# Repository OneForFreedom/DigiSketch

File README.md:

# DigiSketch
It's an etchasketch, gone digital!

Two rotary knobs, One for X axis and one for Y axis and one switch to reset.

I made this because I saw a video on someone using a physical etchasketch, and I thought to myself, hmmm what if I made that - DIGITAL!

so here it is!

Full 3D Model(s)

# BILL OF MATERIALS (BOM)
| Item                | Price (GBP) | Price (USD) | Link |
|---------------------|-------------|-------------|------|
| Solder              | 1.59        | 2.18        | [Link](https://www.aliexpress.com/item/1005008582739945.html?spm=a2g0o.cart.0.0.57e238dah0co8Q&mp=1&pdp_npi=5%40dis%21GBP%21GBP%201.56%21GBP%201.51%21%21GBP%201.51%21%21%21%40211b6c1917517505945503287e3f4d%2112000045828254978%21ct%21UK%216063356903%21%211%210) |
| Solder Cleaner      | 1.45        | 1.99        | [Link](https://www.aliexpress.com/item/1005008139056408.html?spm=a2g0o.cart.0.0.57e238dah0co8Q&mp=1&pdp_npi=5%40dis%21GBP%21GBP%201.45%21GBP%201.45%21%21GBP%201.31%21%21%21%40211b6c1917517505945503287e3f4d%2112000043955012936%21ct%21UK%216063356903%21%211%210) |
| Solder Holder       | 1.74        | 2.38        | [Link](https://www.aliexpress.com/item/1005008060490020.html?spm=a2g0o.cart.0.0.57e238dah0co8Q&mp=1&pdp_npi=5%40dis%21GBP%21GBP%203.62%21GBP%201.74%21%21GBP%201.57%21%21%21%40211b6c1917517505945503287e3f4d%2112000043495814700%21ct%21UK%216063356903%21%211%210) |
| OLED Screen         | 4           | 5.48        | [Link](https://www.aliexpress.com/item/1005008315281577.html?spm=a2g0o.cart.0.0.57e238daS8hq2S&mp=1&pdp_npi=5%40dis%21GBP%21GBP%206.35%21GBP%204.31%21%21GBP%204.31%21%21%21%40211b80e117517562457068912e2b41%2112000044585026991%21ct%21UK%216063356903%21%211%210) |
| Keycaps             | 1.59        | 2.18        | [Link](https://www.aliexpress.com/item/1005005513800132.html?spm=a2g0o.cart.0.0.57e238daS8hq2S&mp=1&pdp_npi=5%40dis%21GBP%21GBP%201.59%21GBP%201.59%21%21GBP%201.59%21%21%21%40211b80e117517562457068912e2b41%2112000033370341351%21ct%21UK%216063356903%21%211%210) |
| Switches            | 1.1         | 1.51        | [Link](https://www.aliexpress.com/item/1005005371211477.html?spm=a2g0o.cart.0.0.57e238daS8hq2S&mp=1&pdp_npi=5%40dis%21GBP%21GBP%201.10%21GBP%201.10%21%21GBP%201.10%21%21%21%40211b80e117517562457068912e2b41%2112000032783075056%21ct%21UK%216063356903%21%211%210&pdp_ext_f=%7B%22cart2PdpParams%22%3A%7B%22pdpBusinessMode%22%3A%22retail%22%7D%7D) |
| Pico                | 1.71        | 2.34        | [Link](https://www.aliexpress.com/item/1005003371056277.html?spm=a2g0o.cart.0.0.57e238daS8hq2S&mp=1&pdp_npi=5%40dis%21GBP%21GBP%201.71%21GBP%201.71%21%21GBP%201.71%21%21%21%40211b80e117517562457068912e2b41%2112000029224170853%21ct%21UK%216063356903%21%211%210) |
| EC11 Cap            | 1.04        | 1.42        | [Link](https://www.aliexpress.com/item/10000056483250.html?spm=a2g0o.cart.0.0.57e238daS8hq2S&mp=1&pdp_npi=5%40dis%21GBP%21GBP%201.04%21GBP%201.04%21%21GBP%201.04%21%21%21%40211b80e117517562457068912e2b41%2112000046133170771%21ct%21UK%216063356903%21%211%210) |
| EC11                | 1.96        | 2.68        | [Link](https://www.aliexpress.com/item/10000056483250.html?spm=a2g0o.cart.0.0.57e238daS8hq2S&mp=1&pdp_npi=5%40dis%21GBP%21GBP%201.96%21GBP%201.96%21%21GBP%201.96%21%21%21%40211b80e117517563008441721e2b41%2112000046133170768%21ct%21UK%216063356903%21%211%210) |
| Keycap Puller       | 1.72        | 2.36        | [Link](https://www.aliexpress.com/item/1005008979101146.html?spm=a2g0o.cart.0.0.57e238daS8hq2S&mp=1&pdp_npi=5%40dis%21GBP%21GBP%201.72%21GBP%201.72%21%21GBP%201.72%21%21%21%40211b80e117517563008441721e2b41%2112000047438847478%21ct%21UK%216063356903%21%211%210) |
| USB Micro Charger   | 0.88        | 1.21        | [Link](https://www.aliexpress.com/item/1005007138392516.html?spm=a2g0o.cart.0.0.57e238daS8hq2S&mp=1&pdp_npi=5%40dis%21GBP%21GBP%200.91%21GBP%200.91%21%21GBP%200.91%21%21%21%40211b80e117517563008441721e2b41%2112000039538590190%21ct%21UK%216063356903%21%211%210) |
| Grips               | 1.08        | 1.48        | [Link](https://www.aliexpress.com/item/1005007345412012.html?spm=a2g0o.cart.0.0.57e238daS8hq2S&mp=1&pdp_npi=5%40dis%21GBP%21GBP%202.34%21GBP%201.17%21%21GBP%201.17%21%21%21%40211b80e117517563008441721e2b41%2112000040354490148%21ct%21UK%216063356903%21%211%210) |

**Subtotal Items**: 20.43 GBP / 27.72 USD  

**PCB**: 12.09 GBP / 16.57 USD   (JLCPCB)
**Subtotal PCB**: 12.09 GBP / 16.57 USD  

**3D Printing Shipping**: 3.45 GBP / 4.74 USD  (ROYAL MAIL)
**Subtotal Shipping**: 3.45 GBP / 4.74 USD  

**PRICES HAVE CHANGED AS QUANTITIES HAVE BEEN REDUCED AND ALSO SINCE THE COUPON CODE NO LONGER WORKS.**

###  Grand Totals

| Currency | Amount    |
|----------|-----------|
| GBP (£)  | **£35.97** |
| USD ($)  | **$49.28** |

>  *Conversion rate used: £1 = $1.37*
# I'm soo sad the coupon expired, I had to remove 100g of solder and a few O rings 😭

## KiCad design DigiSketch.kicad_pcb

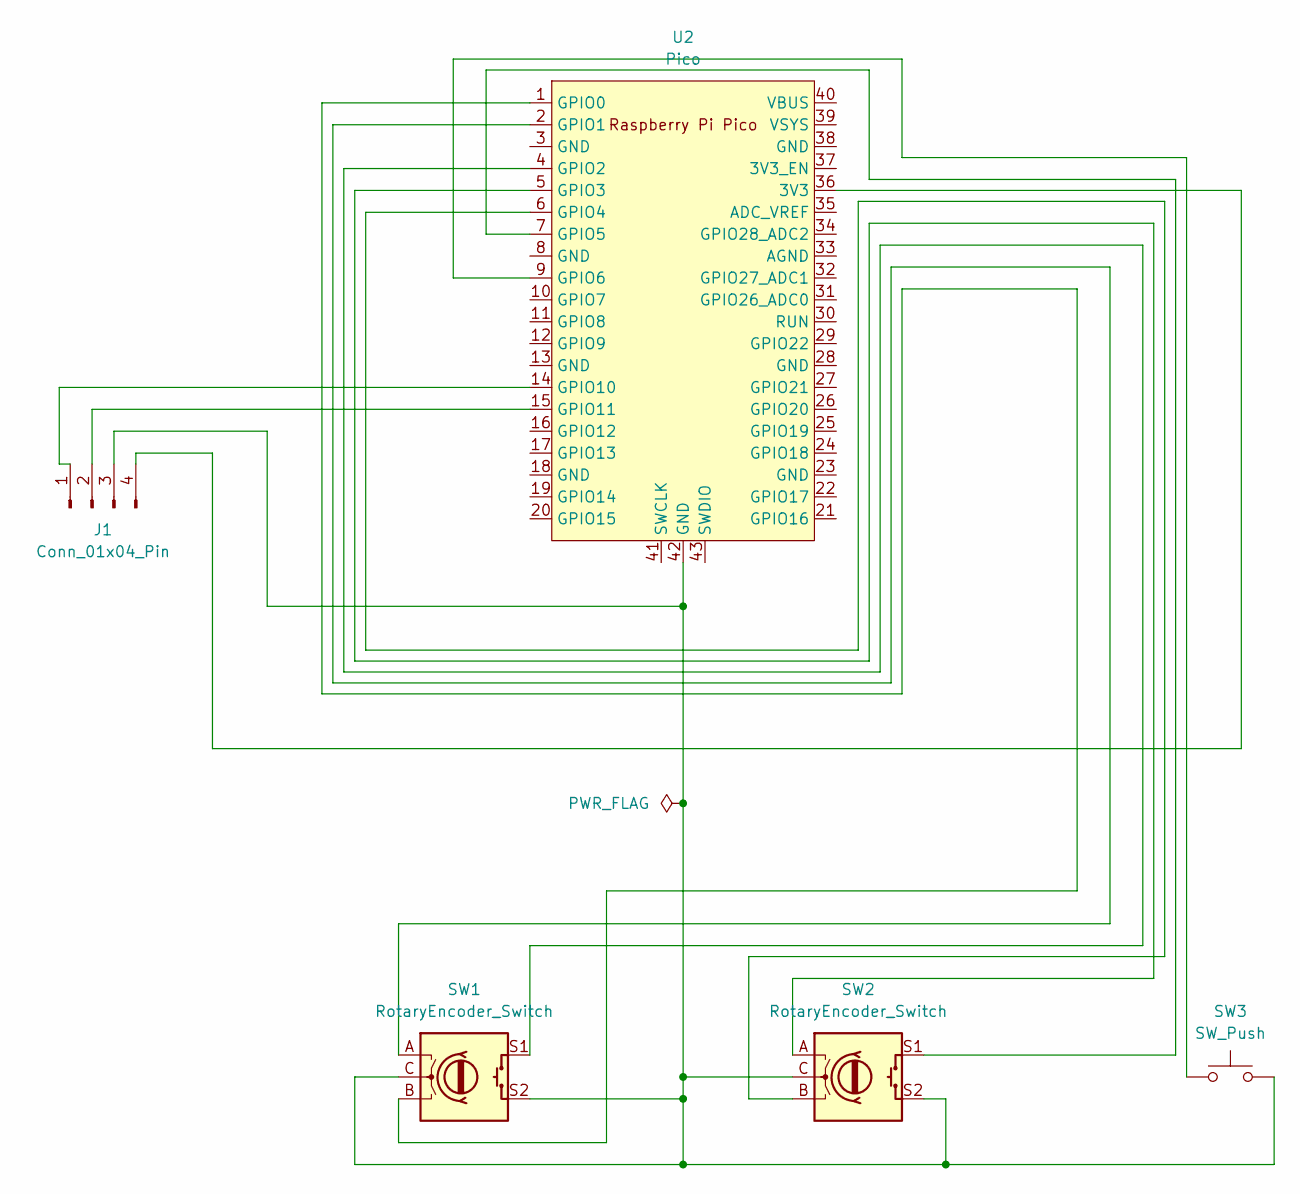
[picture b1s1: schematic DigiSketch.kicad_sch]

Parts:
J1: Conn_01x04_Pin; 128x64OLED
SW1, SW2: RotaryEncoder_Switch; RotaryEncoder_Alps_EC11E-Switch_Vertical_H20mm_MountingHoles
SW3: SW_Push; SW_Cherry_MX_1.00u_PCB
U2: Pico; RPi_Pico_SMD_TH

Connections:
unnamed: J1.1, U2.14 (GPIO10)
unnamed: J1.2, U2.15 (GPIO11)
unnamed: J1.3, SW1.C, SW1.S2, SW2.C, SW2.S2, SW3.2, U2.42 (GND)
unnamed: J1.4, U2.36 (3V3)
unnamed: SW1.B, U2.1 (GPIO0)
unnamed: SW1.A, U2.2 (GPIO1)
unnamed: SW1.S1, U2.4 (GPIO2)
unnamed: SW2.A, U2.5 (GPIO3)
unnamed: SW2.B, U2.6 (GPIO4)
unnamed: SW2.S1, U2.7 (GPIO5)
unnamed: SW3.1, U2.9 (GPIO6)

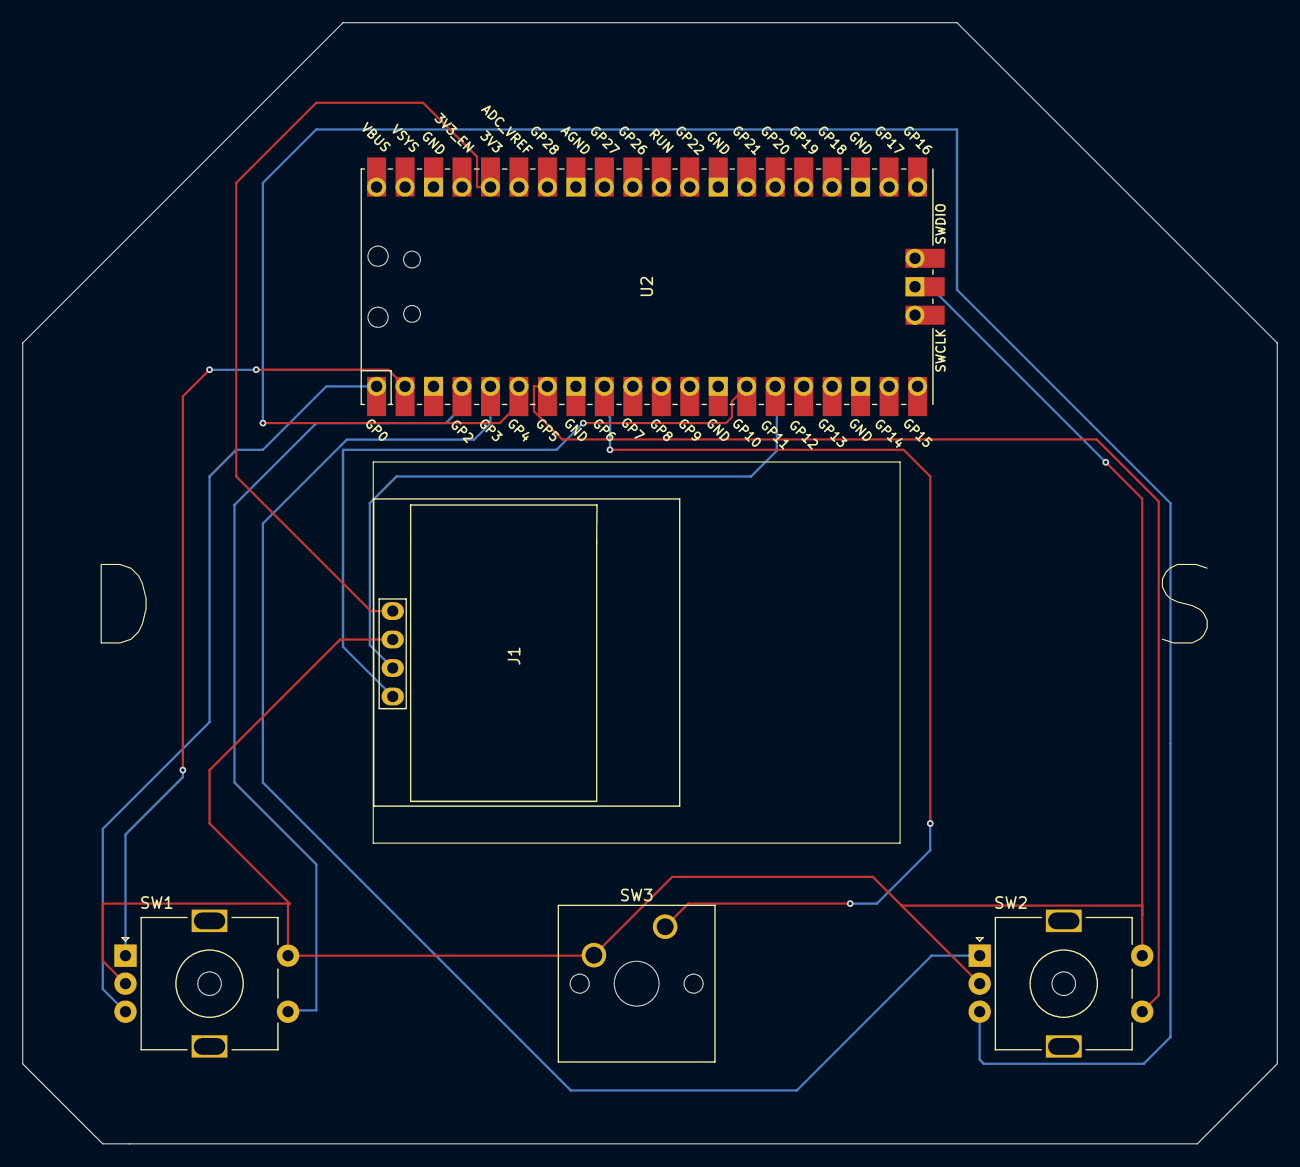
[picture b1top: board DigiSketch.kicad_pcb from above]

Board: 2 copper layers, 111.9 x 100.0 mm, 5 parts (0 on the bottom side), 11 nets.

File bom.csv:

Designator,Footprint,Quantity,Value,LCSC Part #
J1,128x64OLED,1,Conn_01x04_Pin,
"SW1, SW2",RotaryEncoder_Alps_EC11E-Switch_Vertical_H20mm_MountingHoles,2,RotaryEncoder_Switch,
SW3,SW_Cherry_MX_1.00u_PCB,1,SW_Push,
U2,RPi_Pico_SMD_TH,1,Pico,

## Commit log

2025-07-05 Rename b23b2af1c99153fe488ddd7cfa8304c6e30416d8_mx_.step to CherryMxSwitch.step
